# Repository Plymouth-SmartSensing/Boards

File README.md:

# Boards
Boards schematics and gerber

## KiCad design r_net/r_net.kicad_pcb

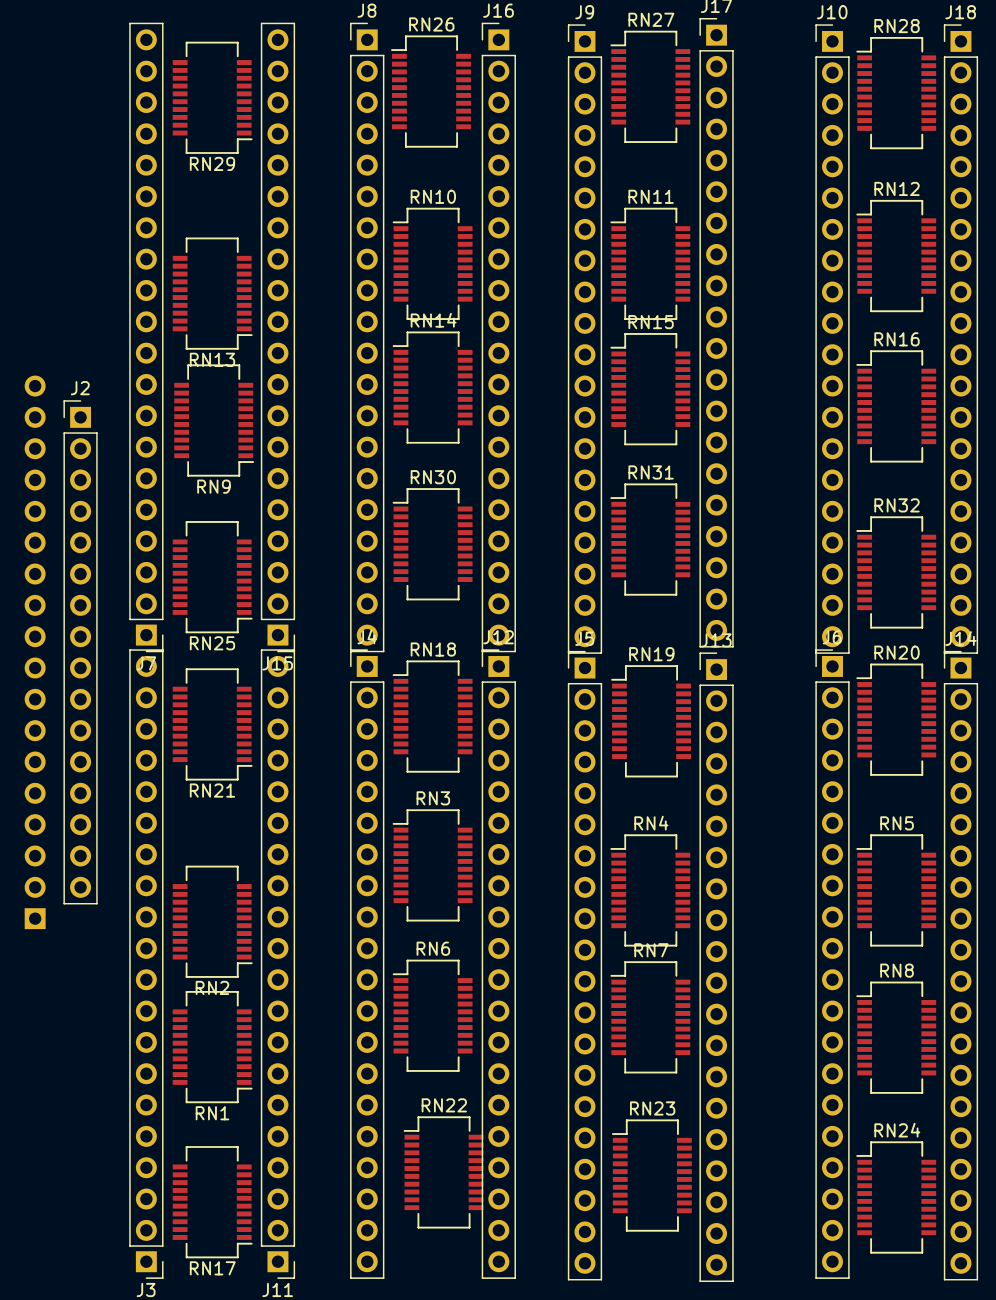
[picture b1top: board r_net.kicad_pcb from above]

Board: 2 copper layers, 50 parts (1 on the bottom side), 337 nets, no tracks yet.

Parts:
J1: Conn_01x18_Female; PinSocket_1x18_P2.54mm_Horizontal
J2: Conn_01x16_Male; PinHeader_1x16_P2.54mm_Vertical
J3, J4, J5, J6, J7, J8, J9, J10, J11, J12, J13, J14, J15, J16, J17, J18: Conn_01x20_Male; PinHeader_1x20_P2.54mm_Vertical
RN1, RN2, RN3, RN4, RN5, RN6, RN7, RN8, RN9, RN10, RN11, RN12, RN13, RN14, RN15, RN16, RN17, RN18, RN19, RN20, RN21, RN22, RN23, RN24, RN25, RN26, RN27, RN28, RN29, RN30, RN31, RN32: R_Pack10; SSOP-20_3.9x8.7mm_P0.635mm

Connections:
5V: J1.1, RN1.20, RN3.20, RN4.20, RN5.20, RN9.20, RN10.20, RN11.20, RN12.20, RN17.20, RN18.20, RN19.20, RN20.20, RN25.20, RN26.20, RN27.20, RN28.20
DIV0: J1.17, J2.1
DIV1: J1.16, J2.2
DIV2: J1.15, J2.3
DIV3: J1.14, J2.4
DIV4: J1.13, J2.5
DIV5: J1.12, J2.6
DIV6: J1.11, J2.7
DIV7: J1.10, J2.8
DIV8: J1.9, J2.9
DIV9: J1.8, J2.10
DIV10: J1.7, J2.11
DIV11: J1.6, J2.12
DIV12: J1.5, J2.13
DIV13: J1.4, J2.14
DIV14: J1.3, J2.15
DIV15: J1.2, J2.16
unnamed: J3.1, RN1.1, RN1.19
unnamed: J3.2, RN1.2, RN1.18
unnamed: J3.3, RN1.3, RN1.17
unnamed: J3.4, RN1.4, RN1.16
unnamed: J3.5, RN1.5, RN1.15
unnamed: J3.6, RN1.6, RN1.14
unnamed: J3.7, RN1.7, RN1.13
unnamed: J3.8, RN1.8, RN1.12
unnamed: J3.9, RN1.9, RN1.11
unnamed: J3.10, RN1.10, RN2.20
unnamed: J3.11, RN2.1, RN2.19
unnamed: J3.12, RN2.2, RN2.18
unnamed: J3.13, RN2.3, RN2.17
unnamed: J3.14, RN2.4, RN2.16
unnamed: J3.15, RN2.5, RN2.15
unnamed: J3.16, RN2.6, RN2.14
unnamed: J3.17, RN2.7, RN2.13
unnamed: J3.18, RN2.8, RN2.12
unnamed: J3.19, RN2.9, RN2.11
unnamed: J3.20, RN2.10
unnamed: J4.1, RN3.1, RN3.19
unnamed: J4.2, RN3.2, RN3.18
unnamed: J4.3, RN3.3, RN3.17
unnamed: J4.4, RN3.4, RN3.16
unnamed: J4.5, RN3.5, RN3.15
unnamed: J4.6, RN3.6, RN3.14
unnamed: J4.7, RN3.7, RN3.13
unnamed: J4.8, RN3.8, RN3.12
unnamed: J4.9, RN3.9, RN3.11
unnamed: J4.10, RN3.10, RN6.20
unnamed: J4.11, RN6.1, RN6.19
unnamed: J4.12, RN6.2, RN6.18
unnamed: J4.13, RN6.3, RN6.17
unnamed: J4.14, RN6.4, RN6.16
unnamed: J4.15, RN6.5, RN6.15
unnamed: J4.16, RN6.6, RN6.14
unnamed: J4.17, RN6.7, RN6.13
unnamed: J4.18, RN6.8, RN6.12
unnamed: J4.19, RN6.9, RN6.11
unnamed: J4.20, RN6.10
unnamed: J5.1, RN4.1, RN4.19
unnamed: J5.2, RN4.2, RN4.18
unnamed: J5.3, RN4.3, RN4.17
unnamed: J5.4, RN4.4, RN4.16
unnamed: J5.5, RN4.5, RN4.15
unnamed: J5.6, RN4.6, RN4.14
unnamed: J5.7, RN4.7, RN4.13
unnamed: J5.8, RN4.8, RN4.12
unnamed: J5.9, RN4.9, RN4.11
unnamed: J5.10, RN4.10, RN7.20
unnamed: J5.11, RN7.1, RN7.19
unnamed: J5.12, RN7.2, RN7.18
unnamed: J5.13, RN7.3, RN7.17
unnamed: J5.14, RN7.4, RN7.16
unnamed: J5.15, RN7.5, RN7.15
unnamed: J5.16, RN7.6, RN7.14
unnamed: J5.17, RN7.7, RN7.13
unnamed: J5.18, RN7.8, RN7.12
unnamed: J5.19, RN7.9, RN7.11
unnamed: J5.20, RN7.10
unnamed: J6.1, RN5.1, RN5.19
unnamed: J6.2, RN5.2, RN5.18
unnamed: J6.3, RN5.3, RN5.17
unnamed: J6.4, RN5.4, RN5.16
unnamed: J6.5, RN5.5, RN5.15
unnamed: J6.6, RN5.6, RN5.14
unnamed: J6.7, RN5.7, RN5.13
unnamed: J6.8, RN5.8, RN5.12
unnamed: J6.9, RN5.9, RN5.11
unnamed: J6.10, RN5.10, RN8.20
unnamed: J6.11, RN8.1, RN8.19
unnamed: J6.12, RN8.2, RN8.18
unnamed: J6.13, RN8.3, RN8.17
unnamed: J6.14, RN8.4, RN8.16
unnamed: J6.15, RN8.5, RN8.15
unnamed: J6.16, RN8.6, RN8.14
unnamed: J6.17, RN8.7, RN8.13
unnamed: J6.18, RN8.8, RN8.12
unnamed: J6.19, RN8.9, RN8.11
unnamed: J6.20, RN8.10
unnamed: J7.1, RN9.1, RN9.19
unnamed: J7.2, RN9.2, RN9.18
unnamed: J7.3, RN9.3, RN9.17
unnamed: J7.4, RN9.4, RN9.16
unnamed: J7.5, RN9.5, RN9.15
unnamed: J7.6, RN9.6, RN9.14
unnamed: J7.7, RN9.7, RN9.13
unnamed: J7.8, RN9.8, RN9.12
unnamed: J7.9, RN9.9, RN9.11
unnamed: J7.10, RN9.10, RN13.20
unnamed: J7.11, RN13.1, RN13.19
unnamed: J7.12, RN13.2, RN13.18
unnamed: J7.13, RN13.3, RN13.17
unnamed: J7.14, RN13.4, RN13.16
unnamed: J7.15, RN13.5, RN13.15
unnamed: J7.16, RN13.6, RN13.14
unnamed: J7.17, RN13.7, RN13.13
unnamed: J7.18, RN13.8, RN13.12
unnamed: J7.19, RN13.9, RN13.11
unnamed: J7.20, RN13.10
unnamed: J8.1, RN10.1, RN10.19
unnamed: J8.2, RN10.2, RN10.18
unnamed: J8.3, RN10.3, RN10.17
unnamed: J8.4, RN10.4, RN10.16
unnamed: J8.5, RN10.5, RN10.15
unnamed: J8.6, RN10.6, RN10.14
unnamed: J8.7, RN10.7, RN10.13
unnamed: J8.8, RN10.8, RN10.12
unnamed: J8.9, RN10.9, RN10.11
unnamed: J8.10, RN10.10, RN14.20
unnamed: J8.11, RN14.1, RN14.19
unnamed: J8.12, RN14.2, RN14.18
unnamed: J8.13, RN14.3, RN14.17
unnamed: J8.14, RN14.4, RN14.16
unnamed: J8.15, RN14.5, RN14.15
unnamed: J8.16, RN14.6, RN14.14
unnamed: J8.17, RN14.7, RN14.13
unnamed: J8.18, RN14.8, RN14.12
unnamed: J8.19, RN14.9, RN14.11
unnamed: J8.20, RN14.10
unnamed: J9.1, RN11.1, RN11.19
unnamed: J9.2, RN11.2, RN11.18
unnamed: J9.3, RN11.3, RN11.17
unnamed: J9.4, RN11.4, RN11.16
unnamed: J9.5, RN11.5, RN11.15
unnamed: J9.6, RN11.6, RN11.14
unnamed: J9.7, RN11.7, RN11.13
unnamed: J9.8, RN11.8, RN11.12
unnamed: J9.9, RN11.9, RN11.11
unnamed: J9.10, RN11.10, RN15.20
unnamed: J9.11, RN15.1, RN15.19
unnamed: J9.12, RN15.2, RN15.18
unnamed: J9.13, RN15.3, RN15.17
unnamed: J9.14, RN15.4, RN15.16
unnamed: J9.15, RN15.5, RN15.15
unnamed: J9.16, RN15.6, RN15.14
unnamed: J9.17, RN15.7, RN15.13
unnamed: J9.18, RN15.8, RN15.12
unnamed: J9.19, RN15.9, RN15.11
unnamed: J9.20, RN15.10
unnamed: J10.1, RN12.1, RN12.19
unnamed: J10.2, RN12.2, RN12.18
unnamed: J10.3, RN12.3, RN12.17
unnamed: J10.4, RN12.4, RN12.16
unnamed: J10.5, RN12.5, RN12.15
unnamed: J10.6, RN12.6, RN12.14
unnamed: J10.7, RN12.7, RN12.13
unnamed: J10.8, RN12.8, RN12.12
unnamed: J10.9, RN12.9, RN12.11
unnamed: J10.10, RN12.10, RN16.20
unnamed: J10.11, RN16.1, RN16.19
unnamed: J10.12, RN16.2, RN16.18
unnamed: J10.13, RN16.3, RN16.17
unnamed: J10.14, RN16.4, RN16.16
unnamed: J10.15, RN16.5, RN16.15
unnamed: J10.16, RN16.6, RN16.14
unnamed: J10.17, RN16.7, RN16.13
unnamed: J10.18, RN16.8, RN16.12
unnamed: J10.19, RN16.9, RN16.11
unnamed: J10.20, RN16.10
unnamed: J11.1, RN17.1, RN17.19
unnamed: J11.2, RN17.2, RN17.18
unnamed: J11.3, RN17.3, RN17.17
unnamed: J11.4, RN17.4, RN17.16
unnamed: J11.5, RN17.5, RN17.15
unnamed: J11.6, RN17.6, RN17.14
unnamed: J11.7, RN17.7, RN17.13
unnamed: J11.8, RN17.8, RN17.12
unnamed: J11.9, RN17.9, RN17.11
unnamed: J11.10, RN17.10, RN21.20
unnamed: J11.11, RN21.1, RN21.19
unnamed: J11.12, RN21.2, RN21.18
unnamed: J11.13, RN21.3, RN21.17
unnamed: J11.14, RN21.4, RN21.16
unnamed: J11.15, RN21.5, RN21.15
unnamed: J11.16, RN21.6, RN21.14
unnamed: J11.17, RN21.7, RN21.13
unnamed: J11.18, RN21.8, RN21.12
unnamed: J11.19, RN21.9, RN21.11
unnamed: J11.20, RN21.10
unnamed: J12.1, RN18.1, RN18.19
unnamed: J12.2, RN18.2, RN18.18
unnamed: J12.3, RN18.3, RN18.17
unnamed: J12.4, RN18.4, RN18.16
unnamed: J12.5, RN18.5, RN18.15
unnamed: J12.6, RN18.6, RN18.14
unnamed: J12.7, RN18.7, RN18.13
unnamed: J12.8, RN18.8, RN18.12
unnamed: J12.9, RN18.9, RN18.11
unnamed: J12.10, RN18.10, RN22.20
unnamed: J12.11, RN22.1, RN22.19
unnamed: J12.12, RN22.2, RN22.18
unnamed: J12.13, RN22.3, RN22.17
unnamed: J12.14, RN22.4, RN22.16
unnamed: J12.15, RN22.5, RN22.15
unnamed: J12.16, RN22.6, RN22.14
unnamed: J12.17, RN22.7, RN22.13
unnamed: J12.18, RN22.8, RN22.12
unnamed: J12.19, RN22.9, RN22.11
unnamed: J12.20, RN22.10
unnamed: J13.1, RN19.1, RN19.19
unnamed: J13.2, RN19.2, RN19.18
unnamed: J13.3, RN19.3, RN19.17
unnamed: J13.4, RN19.4, RN19.16
unnamed: J13.5, RN19.5, RN19.15
unnamed: J13.6, RN19.6, RN19.14
unnamed: J13.7, RN19.7, RN19.13
unnamed: J13.8, RN19.8, RN19.12
unnamed: J13.9, RN19.9, RN19.11
unnamed: J13.10, RN19.10, RN23.20
unnamed: J13.11, RN23.1, RN23.19
unnamed: J13.12, RN23.2, RN23.18
unnamed: J13.13, RN23.3, RN23.17
unnamed: J13.14, RN23.4, RN23.16
unnamed: J13.15, RN23.5, RN23.15
unnamed: J13.16, RN23.6, RN23.14
unnamed: J13.17, RN23.7, RN23.13
unnamed: J13.18, RN23.8, RN23.12
unnamed: J13.19, RN23.9, RN23.11
unnamed: J13.20, RN23.10
unnamed: J14.1, RN20.1, RN20.19
unnamed: J14.2, RN20.2, RN20.18
unnamed: J14.3, RN20.3, RN20.17
unnamed: J14.4, RN20.4, RN20.16
unnamed: J14.5, RN20.5, RN20.15
unnamed: J14.6, RN20.6, RN20.14
unnamed: J14.7, RN20.7, RN20.13
unnamed: J14.8, RN20.8, RN20.12
unnamed: J14.9, RN20.9, RN20.11
unnamed: J14.10, RN20.10, RN24.20
unnamed: J14.11, RN24.1, RN24.19
unnamed: J14.12, RN24.2, RN24.18
unnamed: J14.13, RN24.3, RN24.17
unnamed: J14.14, RN24.4, RN24.16
unnamed: J14.15, RN24.5, RN24.15
unnamed: J14.16, RN24.6, RN24.14
unnamed: J14.17, RN24.7, RN24.13
unnamed: J14.18, RN24.8, RN24.12
unnamed: J14.19, RN24.9, RN24.11
unnamed: J14.20, RN24.10
unnamed: J15.1, RN25.1, RN25.19
unnamed: J15.2, RN25.2, RN25.18
unnamed: J15.3, RN25.3, RN25.17
unnamed: J15.4, RN25.4, RN25.16
unnamed: J15.5, RN25.5, RN25.15
unnamed: J15.6, RN25.6, RN25.14
unnamed: J15.7, RN25.7, RN25.13
unnamed: J15.8, RN25.8, RN25.12
unnamed: J15.9, RN25.9, RN25.11
unnamed: J15.10, RN25.10, RN29.20
unnamed: J15.11, RN29.1, RN29.19
unnamed: J15.12, RN29.2, RN29.18
unnamed: J15.13, RN29.3, RN29.17
unnamed: J15.14, RN29.4, RN29.16
unnamed: J15.15, RN29.5, RN29.15
unnamed: J15.16, RN29.6, RN29.14
unnamed: J15.17, RN29.7, RN29.13
unnamed: J15.18, RN29.8, RN29.12
unnamed: J15.19, RN29.9, RN29.11
unnamed: J15.20, RN29.10
unnamed: J16.1, RN26.1, RN26.19
unnamed: J16.2, RN26.2, RN26.18
unnamed: J16.3, RN26.3, RN26.17
unnamed: J16.4, RN26.4, RN26.16
unnamed: J16.5, RN26.5, RN26.15
unnamed: J16.6, RN26.6, RN26.14
unnamed: J16.7, RN26.7, RN26.13
unnamed: J16.8, RN26.8, RN26.12
unnamed: J16.9, RN26.9, RN26.11
unnamed: J16.10, RN26.10, RN30.20
unnamed: J16.11, RN30.1, RN30.19
unnamed: J16.12, RN30.2, RN30.18
unnamed: J16.13, RN30.3, RN30.17
unnamed: J16.14, RN30.4, RN30.16
unnamed: J16.15, RN30.5, RN30.15
unnamed: J16.16, RN30.6, RN30.14
unnamed: J16.17, RN30.7, RN30.13
unnamed: J16.18, RN30.8, RN30.12
unnamed: J16.19, RN30.9, RN30.11
unnamed: J16.20, RN30.10
unnamed: J17.1, RN27.1, RN27.19
unnamed: J17.2, RN27.2, RN27.18
unnamed: J17.3, RN27.3, RN27.17
unnamed: J17.4, RN27.4, RN27.16
unnamed: J17.5, RN27.5, RN27.15
unnamed: J17.6, RN27.6, RN27.14
unnamed: J17.7, RN27.7, RN27.13
unnamed: J17.8, RN27.8, RN27.12
unnamed: J17.9, RN27.9, RN27.11
unnamed: J17.10, RN27.10, RN31.20
unnamed: J17.11, RN31.1, RN31.19
unnamed: J17.12, RN31.2, RN31.18
unnamed: J17.13, RN31.3, RN31.17
unnamed: J17.14, RN31.4, RN31.16
unnamed: J17.15, RN31.5, RN31.15
unnamed: J17.16, RN31.6, RN31.14
unnamed: J17.17, RN31.7, RN31.13
unnamed: J17.18, RN31.8, RN31.12
unnamed: J17.19, RN31.9, RN31.11
unnamed: J17.20, RN31.10
unnamed: J18.1, RN28.1, RN28.19
unnamed: J18.2, RN28.2, RN28.18
unnamed: J18.3, RN28.3, RN28.17
unnamed: J18.4, RN28.4, RN28.16
unnamed: J18.5, RN28.5, RN28.15
unnamed: J18.6, RN28.6, RN28.14
unnamed: J18.7, RN28.7, RN28.13
unnamed: J18.8, RN28.8, RN28.12
unnamed: J18.9, RN28.9, RN28.11
unnamed: J18.10, RN28.10, RN32.20
unnamed: J18.11, RN32.1, RN32.19
unnamed: J18.12, RN32.2, RN32.18
unnamed: J18.13, RN32.3, RN32.17
unnamed: J18.14, RN32.4, RN32.16
unnamed: J18.15, RN32.5, RN32.15
unnamed: J18.16, RN32.6, RN32.14
unnamed: J18.17, RN32.7, RN32.13
unnamed: J18.18, RN32.8, RN32.12
unnamed: J18.19, RN32.9, RN32.11
unnamed: J18.20, RN32.10

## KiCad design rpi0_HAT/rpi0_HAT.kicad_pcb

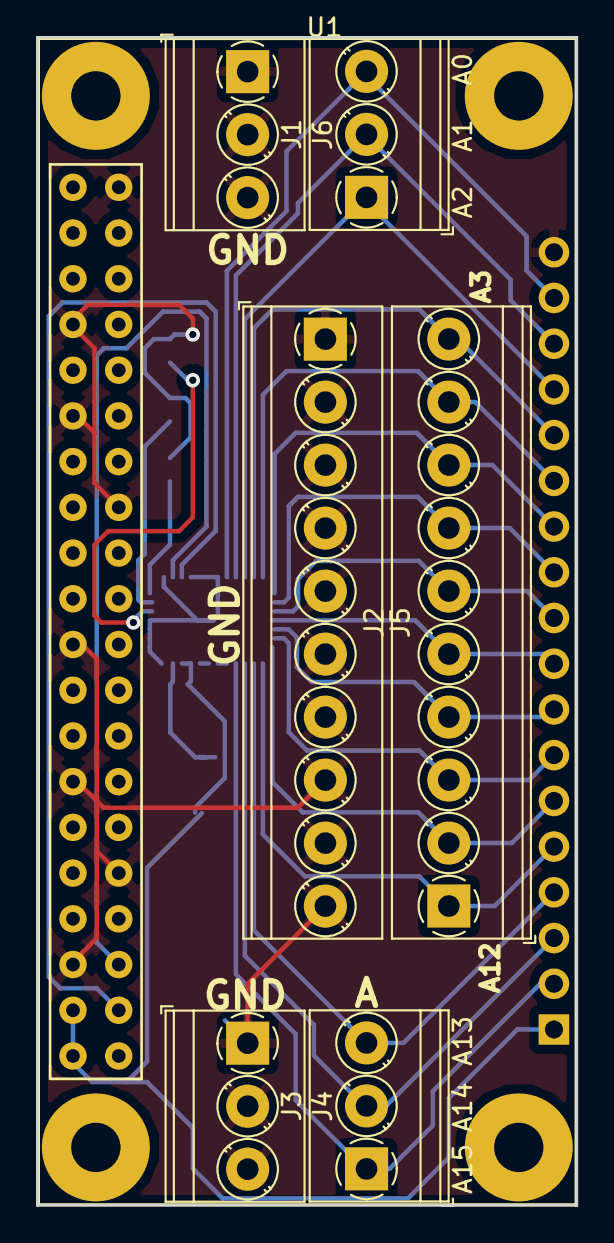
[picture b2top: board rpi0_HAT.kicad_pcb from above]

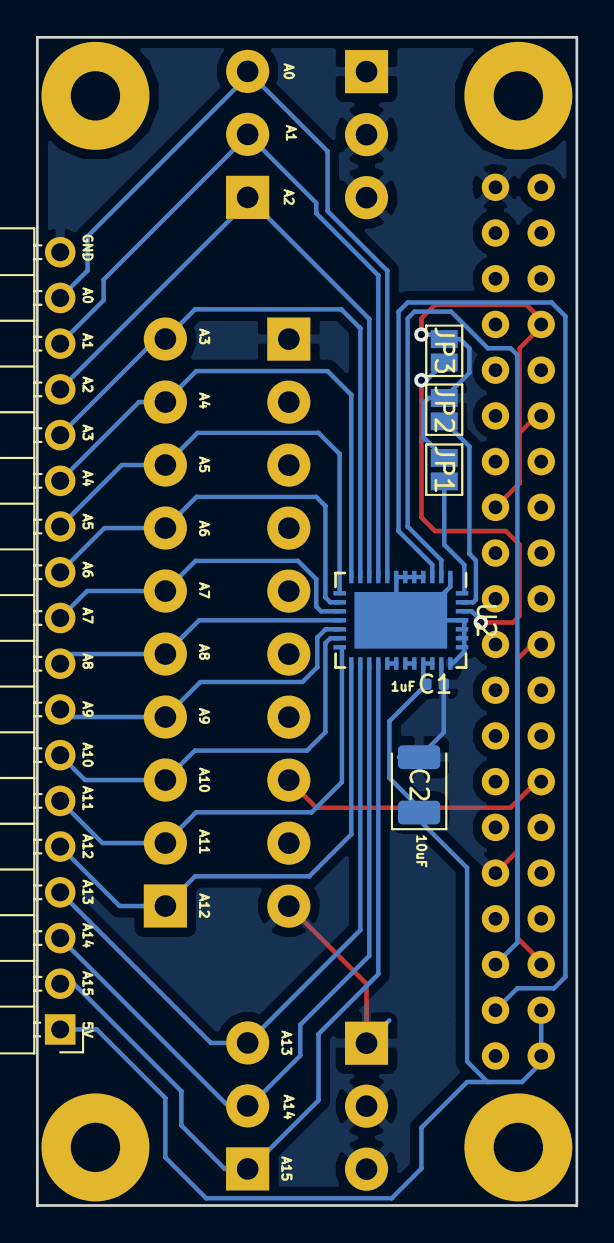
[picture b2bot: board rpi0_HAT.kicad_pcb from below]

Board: 2 copper layers, 30.0 x 64.9 mm, 14 parts (7 on the bottom side), 25 nets.

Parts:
C1: 0.1uF; C_0402_1005Metric
C2: 10uF; CP_EIA-3528-21_Kemet-B
J1, J3, J4, J6: Screw_Terminal_01x03; TerminalBlock_Phoenix_PT-1,5-3-3.5-H_1x03_P3.50mm_Horizontal
J2, J5: Screw_Terminal_01x10; TerminalBlock_Phoenix_PT-1,5-10-3.5-H_1x10_P3.50mm_Horizont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
J7: Conn_01x18; PinHeader_1x18_P2.54mm_Horizontal
JP1, JP2, JP3: SolderJumper_2_Open; SolderJumper-2_P1.3mm_Open_Pad1.0x1.5mm
U1: RPI0-Template; RPi0_Template
U2: LTC2495; QFN-38-1EP_5x7mm_P0.5mm_EP3.15x5.15mm

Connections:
5V: C1.1, C2.1, J7.1, U1.2, U1.4, U2.28, U2.29
DIV0: J1.3, J7.17, U2.8
DIV1: J1.2, J7.16, U2.9
DIV2: J1.1, J7.15, U2.10
DIV3: J2.10, J7.14, U2.11
DIV4: J2.9, J7.13, U2.12
DIV5: J2.8, J7.12, U2.13
DIV6: J2.7, J7.11, U2.14
DIV7: J2.6, J7.10, U2.15
DIV8: J2.5, J7.9, U2.16
DIV9: J2.4, J7.8, U2.17
DIV10: J2.3, J7.7, U2.18
DIV11: J2.2, J7.6, U2.19
DIV12: J2.1, J7.5, U2.20
DIV13: J3.3, J7.4, U2.21
DIV14: J3.2, J7.3, U2.22
DIV15: J3.1, J7.2, U2.23
GND: C1.2, C2.2, J4.1, J4.2, J4.3, J5.1, J5.2, J5.3, J5.4, J5.5, J5.6, J5.7, J5.8, J5.9, J5.10, J6.1, J6.2, J6.3, J7.18, JP1.1, JP2.1, JP3.1, U1.6, U1.9, U1.14, U1.20, U1.25, U1.30, U1.34, U1.39, U2.1, U2.4, U2.5, U2.6, U2.7, U2.30, U2.31, U2.32, U2.33, U2.34, U2.35, U2.39
unnamed: JP1.2, U2.38
unnamed: JP2.2, U2.37
unnamed: JP3.2, U2.36
unnamed: U2.24, U2.25
unnamed: U2.26, U2.27
SCL: U1.5, U2.2
SDA: U1.3, U2.3

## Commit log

2018-10-31 Create LICENSE
2018-10-31 Added rpi0 hat and r_net
2018-10-31 Added pictures of the final product
2018-11-01 Added gerber zip file
